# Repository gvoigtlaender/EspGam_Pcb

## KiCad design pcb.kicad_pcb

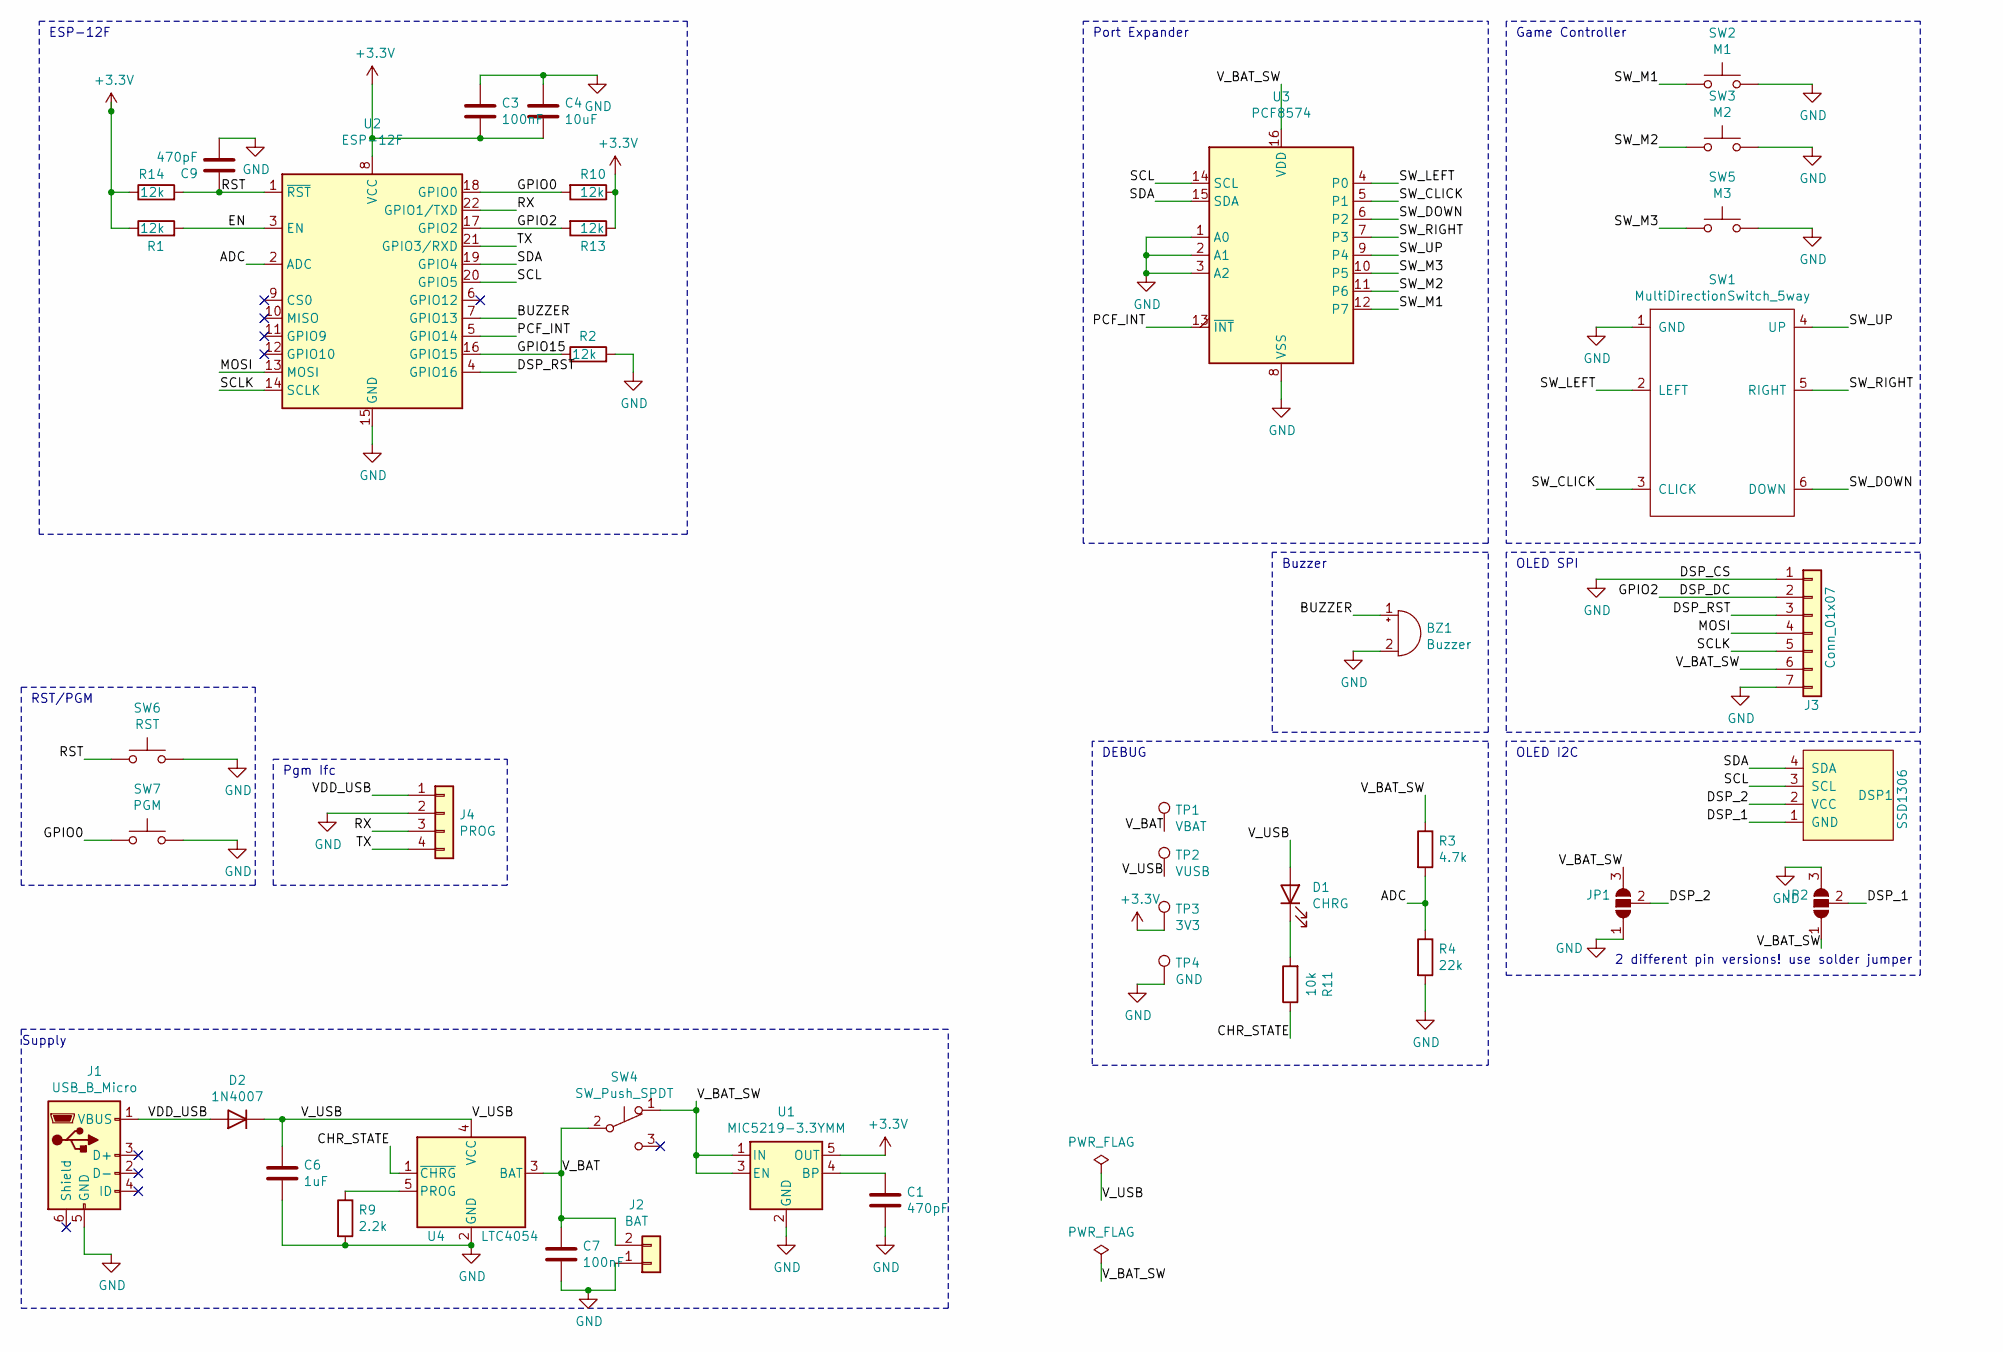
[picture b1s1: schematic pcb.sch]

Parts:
BZ1: Buzzer; Buzzer_Mallory_AST1109MLTRQ
C1, C9: 470pF; C_0805_2012Metric
C3, C7: 100nF; C_0805_2012Metric
C4: 10uF; C_0805_2012Metric
C6: 1uF; C_0805_2012Metric
D1: CHRG; LED_0805_2012Metric_Pad1.15x1.40mm_HandSolder
D2: 1N4007; D_SMA_Handsoldering
DSP1: SSD1306; 128x64OLED
J1: USB_B_Micro; USB_Micro-Socket
J2: BAT; JST-PH-2-SMT-RA
J3: Conn_01x07; PinHeader_1x07_P2.54mm_Vertical
J4: PROG; JST-PH-4-SMT-RA
JP1, JP2: SolderJumper-3_P1.3mm_Open_RoundedPad1.0x1.5mm_NumberLabels
R1, R2, R10, R13, R14: 12k; R_0805_2012Metric
R3: 4.7k; R_0805_2012Metric
R4: 22k; R_0805_2012Metric
R9: 2.2k; R_0805_2012Metric
R11: 10k; R_0805_2012Metric
SW1: MultiDirectionSwitch_5way
SW2: M1; SW_SPST_SKQG_WithoutStem
SW3: M2; SW_SPST_SKQG_WithoutStem
SW4: SW_Push_SPDT; SW_SPDT_PCM12
SW5: M3; SW_SPST_SKQG_WithoutStem
SW6: RST; SW_Push_SPST_NO_Alps_SKRK
SW7: PGM; SW_Push_SPST_NO_Alps_SKRK
TP1: VBAT; TestPoint_THTPad_D1.0mm_Drill0.5mm
TP2: VUSB; TestPoint_THTPad_D1.0mm_Drill0.5mm
TP3: 3V3; TestPoint_THTPad_D1.0mm_Drill0.5mm
TP4: GND; TestPoint_THTPad_D1.0mm_Drill0.5mm
U1: MIC5219-3.3YMM; SOT-23-5
U2: ESP-12F; ESP-12E
U3: PCF8574; SOIC-16W_7.5x10.3mm_P1.27mm
U4: LTC4054; SOT-23-5

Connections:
+3V3: C3.2, C4.2, R1.1, R10.1, R13.1, R14.1, TP3.1, U1.5 (OUT), U2.8 (VCC)
/ADC: R3.2, R4.1, U2.2 (ADC)
/BUZZER: BZ1.1 (-), U2.7 (GPIO13)
/CHR_STATE: R11.1, U4.1 (~CHRG)
/DSP_1: DSP1.1 (GND), JP2.2 (C)
/DSP_2: DSP1.2 (VCC), JP1.2 (C)
/DSP_DC: J3.2, R13.2, U2.17 (GPIO2)
/DSP_RST: J3.3, U2.4 (GPIO16)
/EN: R1.2, U2.3 (EN)
/GPIO0: R10.2, SW7.1, U2.18 (GPIO0)
/GPIO15: R2.1, U2.16 (GPIO15)
/MOSI: J3.4, U2.13 (MOSI)
/PCF_INT: U2.5 (GPIO14), U3.13 (~INT~)
/RST: C9.1, R14.2, SW6.1, U2.1 (~RST)
/RX: J4.3, U2.22 (GPIO1/TXD)
/SCL: DSP1.3 (SCL), U2.20 (GPIO5), U3.14 (SCL)
/SCLK: J3.5, U2.14 (SCLK)
/SDA: DSP1.4 (SDA), U2.19 (GPIO4), U3.15 (SDA)
/SW_CLICK: SW1.3 (CLICK), U3.5 (P1)
/SW_DOWN: SW1.6 (DOWN), U3.6 (P2)
/SW_LEFT: SW1.2 (LEFT), U3.4 (P0)
/SW_M1: SW2.1, U3.12 (P7)
/SW_M2: SW3.1, U3.11 (P6)
/SW_M3: SW5.1, U3.10 (P5)
/SW_RIGHT: SW1.5 (RIGHT), U3.7 (P3)
/SW_UP: SW1.4 (UP), U3.9 (P4)
/TX: J4.4, U2.21 (GPIO3/RXD)
/VDD_USB: D2.2 (A), J1.1 (VBUS), J4.1
/V_BAT: C7.1, J2.2, SW4.2 (B), TP1.1, U4.3 (BAT)
/V_BAT_SW: J3.6, JP1.3 (B), JP2.1 (A), R3.1, SW4.1 (A), U1.1 (IN), U1.3 (EN), U3.16 (VDD)
/V_USB: C6.1, D1.2 (A), D2.1 (K), TP2.1, U4.4 (VCC)
GND: BZ1.2 (+), C1.2, C3.1, C4.1, C6.2, C7.2, C9.2, J1.5 (GND), J2.1, J3.1, J3.7, J4.2, JP1.1 (A), JP2.3 (B), R2.2, R4.2, R9.2, SW1.1 (GND), SW2.2, SW3.2, SW5.2, SW6.2, SW7.2, TP4.1, U1.2 (GND), U2.15 (GND), U3.1 (A0), U3.2 (A1), U3.3 (A2), U3.8 (VSS), U4.2 (GND)
unnamed: C1.1, U1.4 (BP)
unnamed: D1.1 (K), R11.2
unnamed: R9.1, U4.5 (PROG)

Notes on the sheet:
Supply
Pgm Ifc
RST/PGM
Game Controller
Port Expander
OLED SPI
OLED I2C
2 different pin versions! use solder jumper
Buzzer
DEBUG
ESP-12F

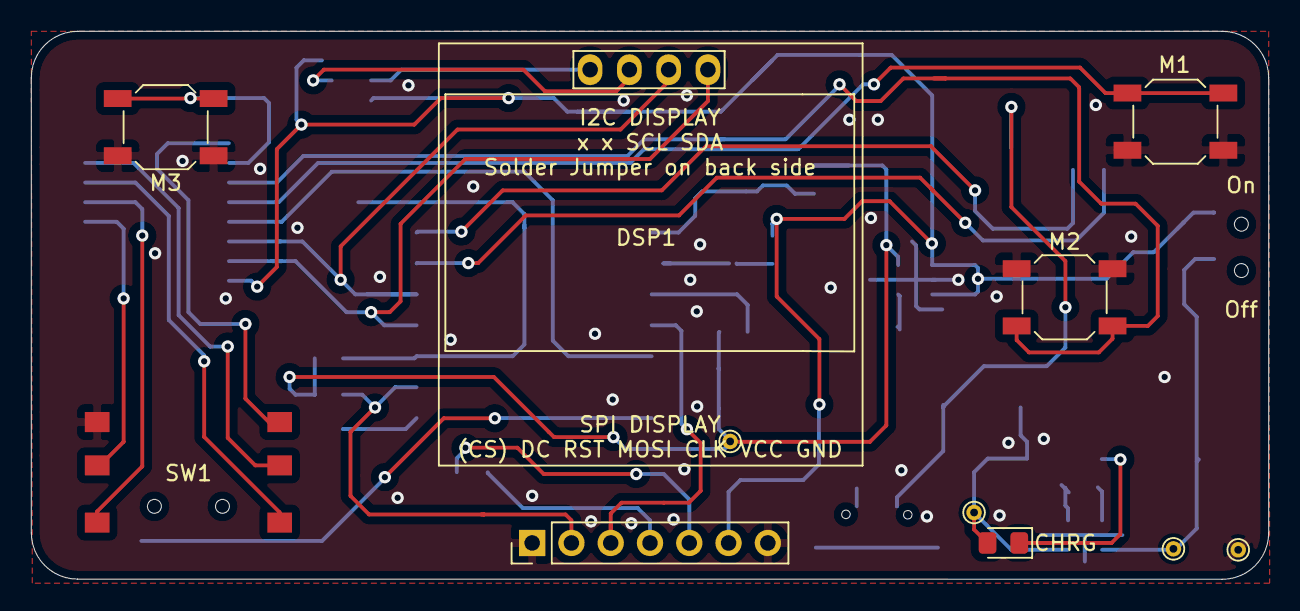
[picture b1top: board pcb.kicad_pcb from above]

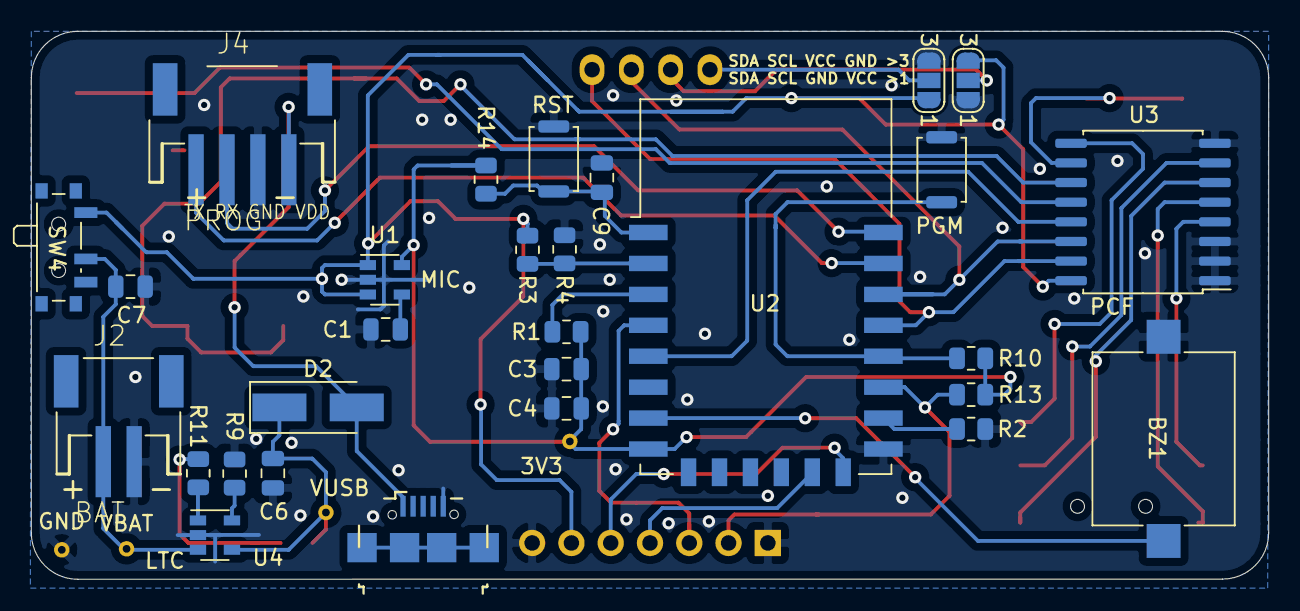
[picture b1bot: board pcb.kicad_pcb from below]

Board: 2 copper layers, 80.0 x 35.4 mm, 40 parts (29 on the bottom side), 35 nets.

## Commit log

2021-03-05 fix path
2021-03-05 cleanup schematic
